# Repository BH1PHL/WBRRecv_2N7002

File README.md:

---
title: 使用2N7002的惠斯通电桥再生式(WBR)接收机
author: BH1PHL
---
# 使用2N7002的惠斯通电桥再生式(WBR)接收机
## 基本原理
电路基于N1BYT的WBR接收机，如下图所示。以Q1为核心组成电容三点式振荡电路，RV2和RV5调整是否起振（再生强弱）。L2、C7、C8和6个二极管D1~D6构成振荡槽路。输入信号通过RV1（起可调衰减作用）衰减和L1，馈入L2中间抽头。变容二极管阳极的直流通路由L1提供。

调谐电压由RV3和R10组成的分压器产生。当J4开路时，RV3分出的电压与动触头2位置$a$（取值范围$0\cdots1$，动触头2位于1端时为$0$，位于3端时为$1$）成线性关系($V_\mathrm{out}=V_\mathrm{cc}\cdot\frac{1+10a}{11}$)。由于变容二极管的容量随电压升高降低，并且在高电压时变化较小，故此时RV3动触头在图中下方（多圈电位器开始几圈）时，频率变化较快；动触头在图中上方（多圈电位器后面几圈）时，频率变化较慢。

J4短路时，输出电压和动触头2位置$a$的关系为$V_\mathrm{out}=V_\mathrm{cc}\cdot\frac{1}{1+10(1-a)}$。显然，$a=0$及$a=1$时，输出电压与J4开路时相同，而在中间状态时，变化呈先慢后快趋势。这种趋势比变容二极管的容量变化率随电压的变化趋势更为明显，故此时多圈电位器位于开始几圈时，频率变化较慢；位于后面几圈时，频率变化较快。

原版WBR接收机采用结型场效应管MPF102检波，此处改为MOS型场效应管2N7002。由于2N7002是增强型器件，采用R15、R16、C23组成的分压电路供给栅极偏压。R14的值足够大，因此偏压电路对振荡器的影响极小。Q2工作在$I_\mathrm{d}$非常小的状态，起检波作用。Q3、U2及外围元件构成音频放大器。U1及外围元件构成稳压电源电路（VCC电压9V）。

上图中振荡器和检波器的等效负载电容、C6、L2的两部分构成惠斯通电桥（如下图）。图中L11、L12代表L1的两部分，L21、L22代表L2的两部分，Cl代表振荡器和检波器的等效负载电容，Ct代表槽路电容，V1代表等效输入电压，V2代表等效振荡电压。

图中OSC和INPUT两端电压如下图。

图中INPUT处几乎没有振荡电压（残余量取决于电桥的平衡情况），但从此处馈入的信号仍然能到达图中OSC处（也就是Q1的基极）。从此处馈入信号有如下好处：

1. 天线负载变化对振荡频率几乎没有影响；
2. Q1处于起振状态时，振荡器到天线的泄露极小（一般情况下很容易控制在-70dBm之内）。

电桥平衡时的直流电位由L1下端的接地点提供。RV1对输入信号起衰减作用。

对基极上的外来信号而言，Q1工作在具有正反馈的放大状态，与典型的再生接收机原理相同。在正反馈的作用下，接收的灵敏度和选择性都会得到很大的提高。工作在起振的临界点附近时，接收机的灵敏度和选择性都是最好的。如果Q1工作在刚好起振的状态，还可兼作拍频振荡器，接收CW和SSB信号。

## 工程
工程用KiCad 6.0绘制。使用四层板，尺寸为100mm×50mm。焊装完成后的实物如下图。

工程文件在[此处](WBRRecv_2N7002_20230227.7z)下载，git 仓库在 https://gitee.com/BH1PHL/WBRRecv_2N7002。

## 元器件选择

* 固定电阻均选用0805 1%贴片电阻。
* F1选用0805封装 0.2A自恢复保险丝（注意应选择耐压指标24V或以上者）。FB1选用0805磁珠（1kΩ@100MHz）。这两个元件的值并不关键。
* 二极管D1～D7选用[ES1JL](https://item.szlcsc.com/139984.html)快恢复二极管（山东晶导微电子），也可试用其他型号、其他厂家产品。注意变容二极管D1~D6采用整流二极管代用，不同型号、厂家的整流二极管反向电容特性不尽相同，并联数量需通过试验确定。
* Q1、Q3选用MMBT3904（SOT-23封装）。
* Q2选用[WST2N7002](https://item.szlcsc.com/88113.html)（WINSOK微硕），也可试用其他厂家产品。
* 固定电容均为多层陶瓷电容（MLCC），10uF电容采用1206封装，其余电容采用0805封装。小于等于1nF的电容采用NP0材质，大于1nF的电容采用X7R/X5R材质。电容选用时注意耐压（使用25V以上耐压的是安全的）。
* 可调电容C8选用常见的6mm塑封微调电容（9～30p，绿色）。注意质量不好的此类电容可能会遇到内部开路情况，建议焊机前先测量，或采用类似尺寸陶瓷外壳微调电容。
* 电位器RV1、RV2、RV4选用与ALPS RK097单联同封装产品；RV3选用多圈电位器（如BOURNS 3590S-2），用2.54mm排针引出。RV5选用与BOURNS 3362P同封装产品。
* U1选用数据手册中明示支持陶瓷电容的SOT-223封装1117可调版，如AZ1117、SPX1117、AP1117等。注意如果使用原版LM1117或最常见的AMS1117，C26可能必须采用钽电容。
* U2可采用LM386或任何兼容产品。
* J1采用夹板式SMA插座，J2采用[5脚直插式耳机插座](https://item.szlcsc.com/300204.html)，J3采用3.5mm脚距插拔式接线端子（[插头](https://item.szlcsc.com/376575.html)、[插座](https://item.szlcsc.com/376577.html)），J4采用2.54mm排针配合短路子。
* L1采用$\mu_\mathrm{i}=300$，OD×ID×h=12.7mm×7.9mm×6.4mm的铁氧体磁环绕制，双线并绕2圈。
* L2采用T50-6铁粉芯磁环绕制。不同波段的圈数（均为双线并绕）、C7、J4的情况及频率范围见下表：

|波段|电感 (T50-6)|C7|J4|频率范围|
|--|--|--|--|--|
|40m|17T×2|47p|短路|约6990~7220kHz|
|30m|15T×2|0p|开路|约9.6~10.2MHz|
|20m|11T×2|0p|开路|约13.5~14.4MHz|

## 调整方法
必备设备：电源、信号发生器、耳机或扬声器
可选设备：衰减器、示波器
步骤：
1. REGEN电位器调整到75%；VOLUME电位器调整到中间；TUNE多圈电位器调整到最小。
2. 连接电源、耳机或扬声器、信号发生器，电源设置到12V。
3. 接入0.1mV左右的信号：信号发生器设置到100mVpp+60dB衰减器，ANT电位器调整到最大；或1mVpp+ANT电位器调整到1/10左右。
4. 打开电源和信号发生器。调整VOLUME电位器至音量舒适。
5. 调整再生：调整PRESET微调电位器，使再生刚好起振（耳机内背景噪声从小突然变大）。注意：振荡过强时耳机内声音也可能很小。
6. 调低端覆盖：信号发生器设置到SWEEP模式，起始频率6.5MHz，终止频率7.5MHz，时间0.2s，调整可调电容C8，使耳机中出现声音。调整信号发生器扫频上下限和可调电容C8，缩小频率范围，使TUNE多圈电位器在最小（接收频率最低）时接收频率在6990kHz左右。
7. 确认高端覆盖和再生控制：信号发生器设置到7.2MHz，调整TUNE多圈电位器直到收到信号，调整REGEN电位器确认再生控制仍然起作用（从低向高调整时有一个背景噪声突然变大、啸叫突然出现的点）。
8. 如果需要，用热熔胶或蜡固封线圈（固封后可能需要微调可调电容C8）。

注：
* 第6步粗调也可改为在T50-6磁环内穿线2～3圈并连接示波器或高阻输入的频率计，在再生出现时观察信号频率并调整可调电容。
* 调整（尤其是微调）时，也可将信号输入端连接带频谱功能的成品接收机（如G90S），用接收机看振荡器到天线泄露信号的频率。

## 使用方法

1. 接入天线、电源、耳机或扬声器。电源电压应在10.5V以上，高压限制由所使用的1117和输入保险丝、滤波电容等元件的耐压决定。**注意电源极性！**

2. ANT电位器、VOLUME电位器调整到中间位置。REGEN电位器调整到刚好起振（背景噪声突然变大）的位置。VOLUME电位器调整至音量舒适。注意：没有起振时有广播干扰是正常现象。起振后若还有广播干扰，可适当左旋ANT电位器增加输入衰减量；若无论有无起振均无广播干扰，说明附近无强干扰广播电台，可适当右旋ANT电位器减少输入衰减量。

3. 调整TUNE电位器选台。一般需要同时调整REGEN电位器，以使再生工作在起振点附近，获得最好的接收效果。注意随着调谐频率升高，再生会变强，如果要保持再生强度不变，应当适当左旋REGEN电位器，反之亦然。

4. 接收CW/SSB电台时，再生调节到**刚好起振**的位置（REGEN电位器放在起振点略偏右侧）效果最好；接收AM电台时，再生调节到**刚好不起振**的位置（REGEN电位器放在起振点略偏左侧）效果最好。

----
© BH1PHL 2022~2023

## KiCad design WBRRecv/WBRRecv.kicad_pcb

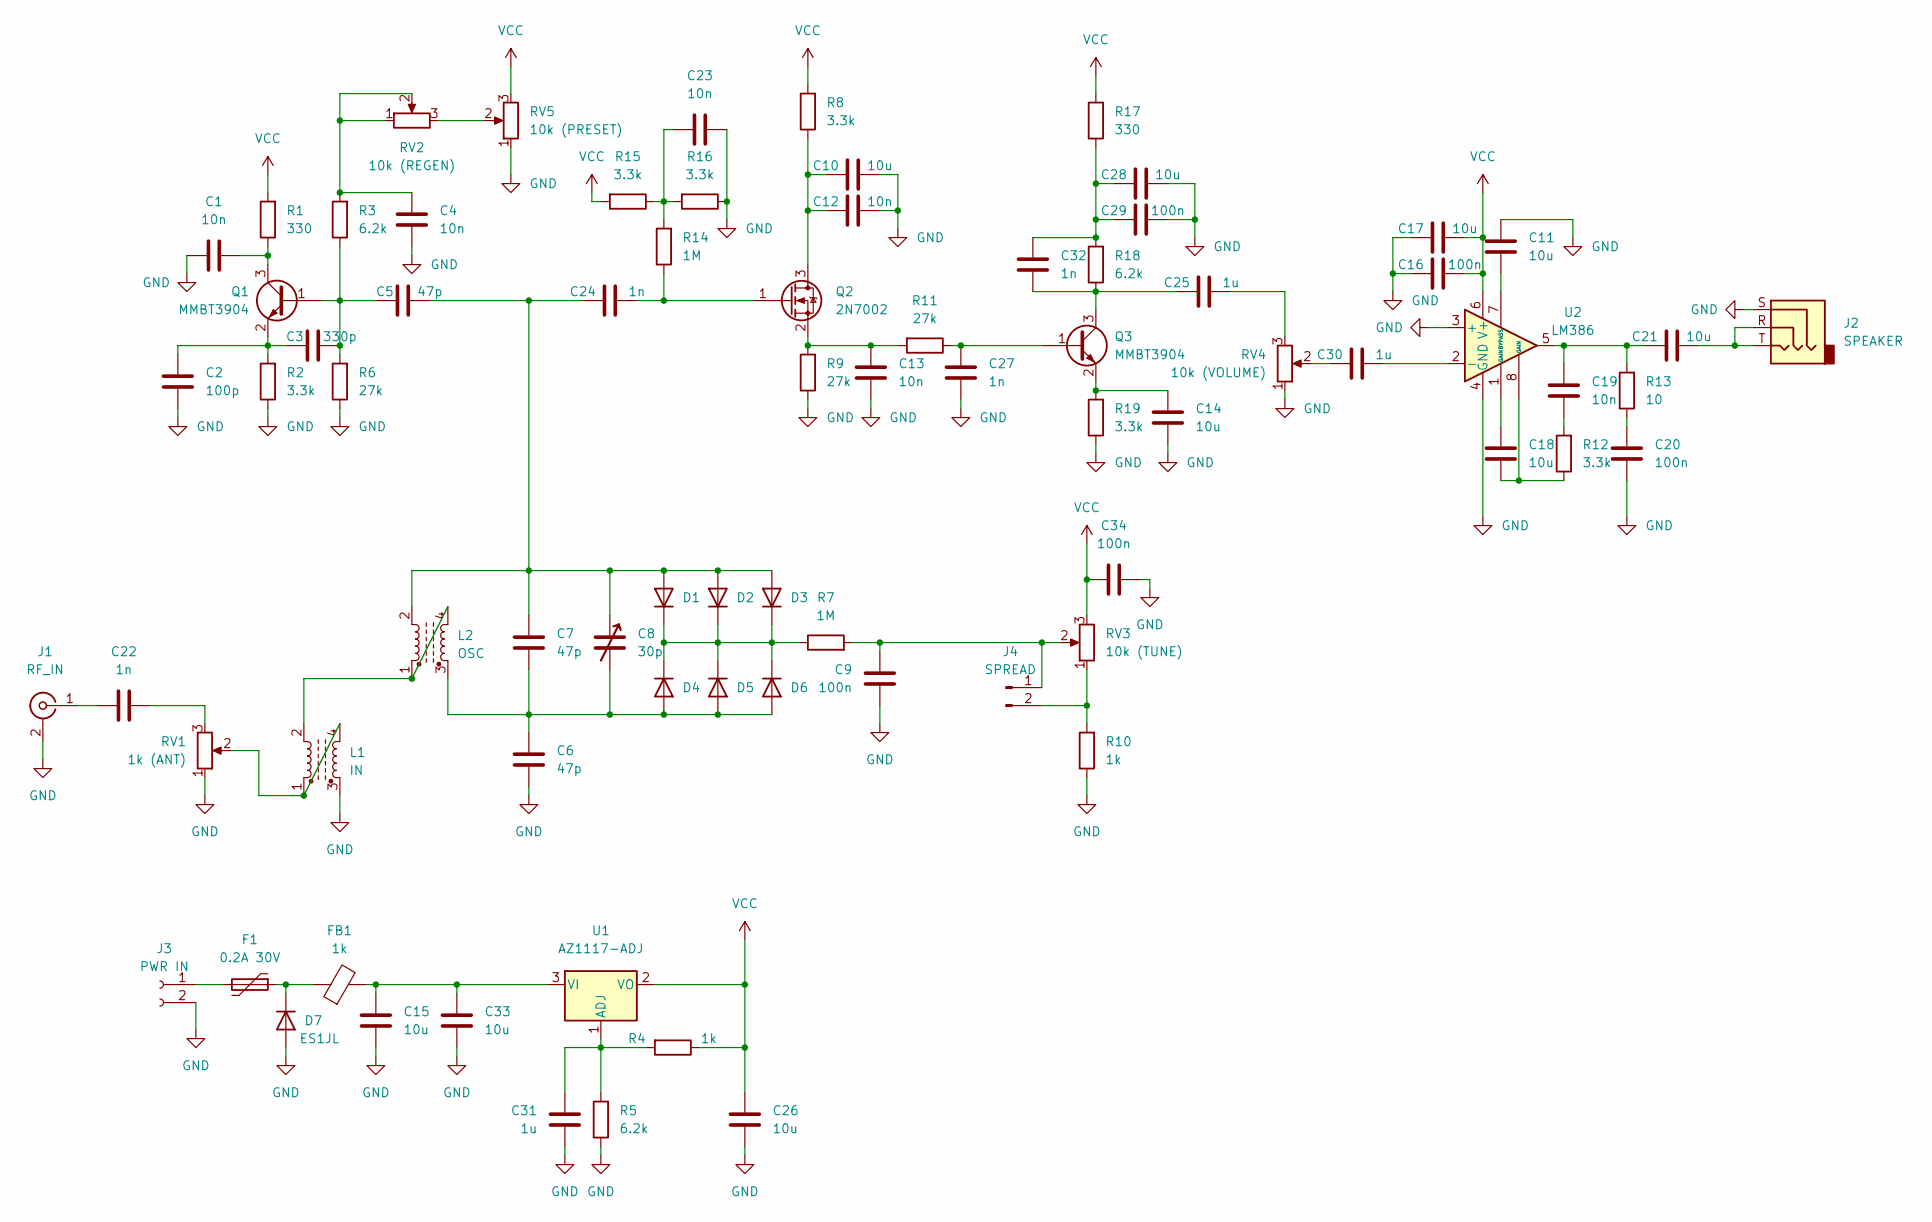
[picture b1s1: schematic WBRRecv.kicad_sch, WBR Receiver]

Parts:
C1, C4, C12, C13, C19, C23: 10n; C_0805_2012Metric
C2: 100p; C_0805_2012Metric
C3: 330p; C_0805_2012Metric
C5, C6, C7: 47p; C_0805_2012Metric
C8: 30p; TRIMMERCAP6-2
C9, C16, C20, C29, C34: 100n; C_0805_2012Metric
C10, C11, C14, C15, C17, C18, C21, C26, C28, C33: 10u; C_1206_3216Metric
C22, C24, C27, C32: 1n; C_0805_2012Metric
C25, C30, C31: 1u; C_0805_2012Metric
D1, D2, D3, D4, D5, D6, D7: ES1JL; D_SOD-123
F1: 0.2A 30V; Fuse_0805_2012Metric
FB1: 1k; L_0805_2012Metric
J1: RF_IN; SMA-EM1
J2: SPEAKER; STEREO_PHONEJACK_5P
J3: PWR IN; DB2ERC-3.5-2P
J4: SPREAD; PinHeader_1x02_P2.54mm_Vertical
L1: IN; TOROID13-4
L2: OSC; TOROID13-4
Q1, Q3: MMBT3904; SOT-23
Q2: 2N7002; SOT-23
R1, R17: 330; R_0805_2012Metric
R2, R8, R12, R15, R16, R19: 3.3k; R_0805_2012Metric
R3, R5, R18: 6.2k; R_0805_2012Metric
R4, R10: 1k; R_0805_2012Metric
R6, R9, R11: 27k; R_0805_2012Metric
R7, R14: 1M; R_0805_2012Metric
R13: 10; R_0805_2012Metric
RV1: 1k (ANT); RK097-SINGLE
RV2: 10k (REGEN); RK097-SINGLE
RV3: 10k (TUNE); PinHeader_1x03_P2.54mm_Vertical
RV4: 10k (VOLUME); RK097-SINGLE
RV5: 10k (PRESET); BOURNS-3362P_pot
U1: AZ1117-ADJ; SOT-223-3_TabPin2
U2: LM386; SO-8_3.9x4.9mm_P1.27mm

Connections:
GND: C1.2, C2.2, C4.2, C6.1, C9.1, C10.1, C11.2, C12.1, C13.1, C14.1, C15.1, C16.2, C17.2, C20.1, C23.1, C26.1, C27.1, C28.1, C29.1, C31.1, C33.1, C34.1, D7.2 (A), J1.2 (Ext), J2.S, J3.2, L1.3, R2.1, R5.1, R6.1, R9.1, R10.1, R16.1, R19.1, RV1.1, RV4.1, RV5.1, U2.3 (+), U2.4 (GND)
unnamed: C1.1, Q1.3 (C), R1.1
unnamed: C2.1, C3.2, Q1.2 (E), R2.2
unnamed: C3.1, C5.2, Q1.1 (B), R3.1, R6.2
unnamed: C4.1, R3.2, RV2.1, RV2.2
unnamed: C6.2, C7.1, C8.2, D4.2 (A), D5.2 (A), D6.2 (A), L2.3
unnamed: C9.2, J4.1, R7.2, RV3.2
unnamed: C10.2, C12.2, Q2.3 (D), R8.1
unnamed: C11.1, U2.7 (BYPASS)
unnamed: C13.2, Q2.2 (S), R9.2, R11.2
unnamed: C14.2, Q3.2 (E), R19.2
unnamed: C15.2, C33.2, FB1.2, U1.3 (VI)
unnamed: C18.1, R12.1, U2.8 (GAIN)
unnamed: C18.2, U2.1 (GAIN)
unnamed: C19.1, R12.2
unnamed: C19.2, C21.2, R13.2, U2.5
unnamed: C20.2, R13.1
unnamed: C21.1, J2.R, J2.T
unnamed: C22.1, J1.1 (In)
unnamed: C22.2, RV1.3
unnamed: C23.2, R14.2, R15.1, R16.2
unnamed: C24.1, Q2.1 (G), R14.1
unnamed: C5.1, C7.2, C8.1, C24.2, D1.2 (A), D2.2 (A), D3.2 (A), L2.2
unnamed: C25.1, RV4.3
unnamed: C25.2, C32.1, Q3.3 (C), R18.1
unnamed: C27.2, Q3.1 (B), R11.1
unnamed: C28.2, C29.2, C32.2, R17.1, R18.2
unnamed: C30.1, U2.2 (-)
unnamed: C30.2, RV4.2
unnamed: C31.2, R4.2, R5.2, U1.1 (ADJ)
unnamed: D1.1 (K), D2.1 (K), D3.1 (K), D4.1 (K), D5.1 (K), D6.1 (K), R7.1
unnamed: D7.1 (K), F1.1, FB1.1
unnamed: F1.2, J3.1
unnamed: J4.2, R10.2, RV3.1
unnamed: L1.1, L1.4, RV1.2
unnamed: L1.2, L2.1, L2.4
unnamed: RV2.3, RV5.2
VCC: C16.1, C17.1, C26.2, C34.2, R1.2, R4.1, R8.2, R15.2, R17.2, RV3.3, RV5.3, U1.2 (VO), U2.6 (V+)

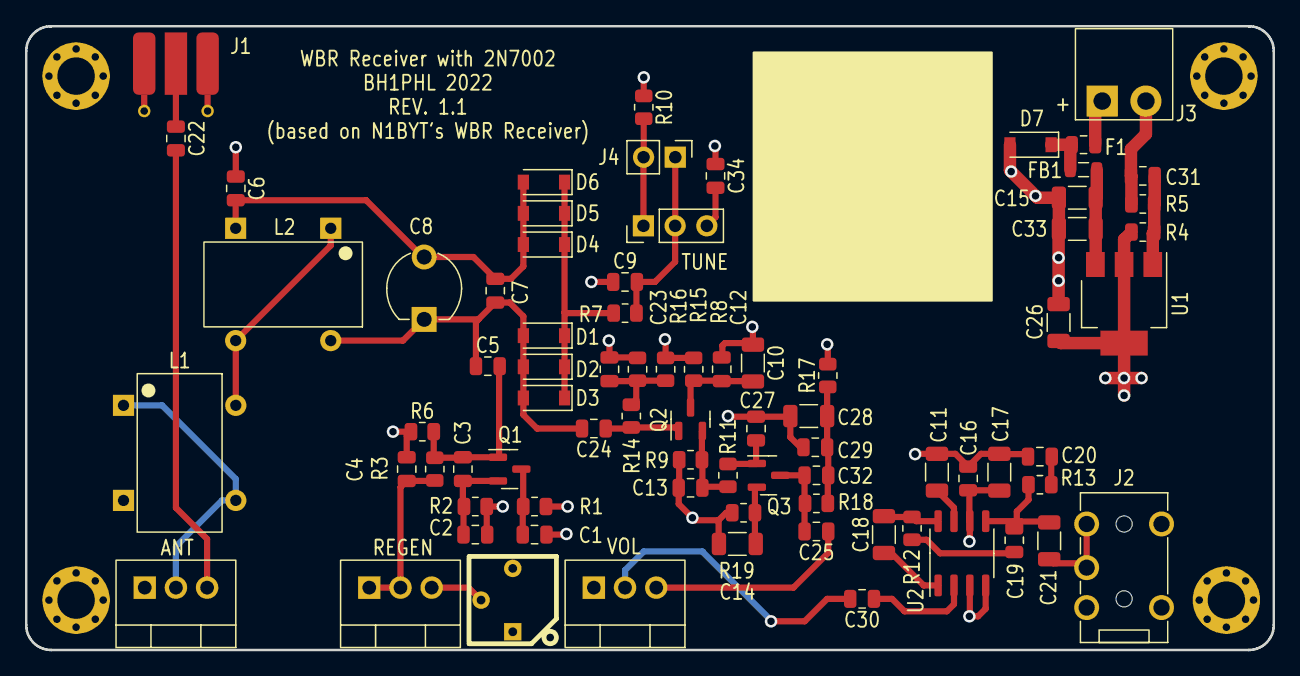
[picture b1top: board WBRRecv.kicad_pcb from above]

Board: 4 copper layers, 100.0 x 50.0 mm, 78 parts (0 on the bottom side), 38 nets.

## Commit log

2022-02-07 Add files
2022-02-07 update README.md.
2022-02-09 modify README.md
2023-02-26 Add English readme file
2023-02-26 update READMEs
2023-02-26 little changes on readmes
